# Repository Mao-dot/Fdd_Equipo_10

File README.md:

<h1 align="center">Equipo 10 — Fundamentos de Diseño</h1>

<p align="center">
  <strong>Ingeniería Informática e Ingeniería Industrial · 2026-2</strong><br />
  Universidad Peruana Cayetano Heredia
</p>

---

## Rediseño de FoodScan

- [Modelo 3D y archivos de fabricación](Proyecto/MóduloMecánico/Rediseño/README.md) · [STEP para Onshape](Proyecto/MóduloMecánico/Rediseño/exports/step/FoodScan_cerrado_Onshape.step)
- [Electrónica revisión A](Proyecto/MóduloElectrónico/Rediseño_FoodScan/README.md) · [Esquemático editable en EasyEDA](Proyecto/MóduloElectrónico/Rediseño_FoodScan/easyeda/FoodScan.epro2)
- [Lista de materiales](Proyecto/MóduloElectrónico/BOM.md) · [Integración de la PCB con la carcasa](Proyecto/MóduloElectrónico/Rediseño_FoodScan/Integracion_mecanica.md)
- [Entrega del Taller 11](Fundamentos%20de%20diseño/Talleres/Taller_11.md)

## 🌍 Descripción del Equipo

Somos el **Equipo 10** del curso **Fundamentos de Diseño 2026-2**, conformado por estudiantes de las carreras de Ingeniería Informática e Industrial.
Nuestro objetivo es aplicar la metodología de diseño para generar soluciones innovadoras con impacto social, tecnológico y ambiental.

---

## 🎯 ODS principal: ODS 12 — Producción y consumo responsables

El Objetivo de Desarrollo Sostenible 12 busca garantizar modalidades de consumo y producción sostenibles. Este objetivo promueve el uso responsable de los recursos, la reducción de residuos y el acceso a información que permita a las personas adoptar decisiones de consumo más conscientes.

### Meta seleccionada: 12.8

La meta 12.8 busca garantizar que, para el año 2030, las personas dispongan de información y conocimientos relevantes que les permitan adoptar estilos de vida sostenibles y en armonía con la naturaleza.

---

## ⚠️ Problemática identificada

En la vida cotidiana, las personas que desean controlar y conocer mejor su alimentación presentan dificultades para obtener información práctica, inmediata y comprensible sobre la cantidad y la composición nutricional de los alimentos que consumen.

Aunque existen tablas nutricionales, aplicaciones y bases de datos, estas herramientas suelen presentar valores correspondientes a cantidades estandarizadas, como 100 gramos o porciones predeterminadas. Por ello, el usuario debe identificar el alimento, estimar la cantidad servida, consultar distintas referencias e introducir manualmente los datos. Este proceso requiere tiempo y conocimientos previos, puede producir estimaciones poco consistentes y dificulta mantener un seguimiento frecuente.

Esta situación resulta especialmente relevante para las personas que realizan actividad física y buscan conocer regularmente la composición de sus comidas, principalmente la cantidad de proteínas, carbohidratos y grasas presentes en las porciones que consumen.

Por lo tanto, el problema no es necesariamente la ausencia de información nutricional, sino la dificultad para relacionar la información general disponible con la cantidad real de alimento presente en una porción cotidiana. Esta limitación puede reducir la capacidad de las personas para comparar sus porciones y tomar decisiones informadas y conscientes sobre su consumo.

---

## 👥 Público objetivo

### Público general

Personas interesadas en conocer mejor las cantidades y la composición nutricional de los alimentos que consumen.

### Público inicial

Personas físicamente activas que realizan un seguimiento frecuente de su alimentación y necesitan consultar información sobre las porciones y los macronutrientes presentes en sus comidas.

---

## 🔗 Relación de la problemática con el ODS 12

La problemática se relaciona con el ODS 12 porque el acceso a información comprensible sobre los alimentos y sus porciones puede favorecer decisiones de consumo más informadas y conscientes.

En particular, se vincula con la meta 12.8, ya que esta plantea la necesidad de que las personas dispongan de información y conocimientos relevantes para adoptar hábitos de consumo responsables. El equipo se enfocará inicialmente en comprender las dificultades que encuentran los usuarios al intentar obtener y utilizar esta información, antes de definir una solución o prototipo.

Para precisar su vínculo con el consumo sostenible, el equipo analizará también si las dificultades para comprender y estimar las porciones influyen en la planificación de las cantidades consumidas y en decisiones que puedan producir consumo excesivo o desperdicio de alimentos. Esta relación se estudiará como parte de la problemática y no se asumirá como un resultado previo.

---

## ❓ Pregunta de investigación

> ¿Cómo facilitar que las personas que desean iniciar o mantener una alimentación controlada reconozcan de manera práctica las cantidades y composición nutricional de los alimentos que consumen? 

---

## 📍 Alcance inicial

El proyecto estudiará el acceso y uso de información nutricional relacionada con porciones cotidianas. En esta etapa no se planteará una solución definitiva ni se abordarán diagnósticos médicos, tratamientos o planes de alimentación personalizados.

---

## 📚 Referencias

1. Naciones Unidas. [Objetivo de Desarrollo Sostenible 12: Producción y consumo responsables](https://sdgs.un.org/goals/goal12).
2. Instituto Nacional de Salud. [Porciones recomendadas](https://alimentacionsaludable.ins.gob.pe/adultos/porciones-recomendadas).
3. Instituto Nacional de Salud. [Aplicación Tablas Peruanas de Composición de Alimentos](https://www.gob.pe/es/38805-acceder-a-informacion-alimenticia-en-la-aplicacion-tablas-peruanas-de-composicion-de-alimentos).
4. Organización de las Naciones Unidas para la Alimentación y la Agricultura. [Food Composition Data: Production, Management and Use](https://www.fao.org/uploads/media/Greenfield_and_shouthgate_2003_English_02.pdf).

---

## 📸 Fotografía del Equipo

---

## 👥 Integrantes del Equipo
| Foto | Nombre | Rol | Intereses |
|:---:|--------|-----|-----------|
|  | **Mao Arceni Capcha Pumacahua** | Líder del equipo | Programación, análisis de datos, simulación |
|  | **Cruz Oyarce Katherine Jireh** | Encargado de documentación | comunicación científica y redacción técnica |
|  | **Lucero Sofía Tarazona Gonzales** | Responsable de investigación | Gestión ambiental, desarrollo comunitario |
|  | **Renzo Jair Cruz Vega** | Diseñador | Diseño de prototipos, creatividad aplicada |
|  | **Julio Maguiña** | Coordinador de investigación | Investigación, análisis y desarrollo de propuestas |

---

## 📌 Resumen Final
Este README resume quiénes somos, el ODS principal seleccionado y la problemática que buscamos comprender durante el curso.

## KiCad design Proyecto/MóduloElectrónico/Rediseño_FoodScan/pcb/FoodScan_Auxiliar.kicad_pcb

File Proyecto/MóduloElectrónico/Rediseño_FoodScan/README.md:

# FoodScan · Rediseño electrónico

Revisión A para prototipo, 12 de noviembre de 2026. La entrega parte de la BOM del rediseño y de su ensamblaje mecánico de trabajo. El sistema utiliza la Adafruit 5838, una DevKitC-1 N16R8 v1.1, el módulo UART Best Modules BMH12M205, el OLED Waveshare 25742 y cuatro tiras COB.

| Archivo | Uso |
| --- | --- |
| [FoodScan.epro2](easyeda/FoodScan.epro2) | Proyecto nativo para EasyEDA Pro 3.2.209, con cuatro hojas, símbolos, huellas y PCB de dos capas enrutada. |
| [Vistas de esquemático](easyeda/vistas/) | Hojas de PCB auxiliar, entrada e iluminación, ESP32 y cámara, y pesaje, pantalla y controles. |
| [PCB editable de KiCad](pcb/FoodScan_Auxiliar.kicad_pcb) | Fuente física de la placa. Las bibliotecas `.pretty`, el archivo `fp-lib-table` y los STEP individuales se incluyen al lado. |
| [STEP poblado](pcb/FoodScan_Auxiliar.step) · [Vista 3D](pcb/FoodScan_Auxiliar.png) | Exportación de la PCB real, para revisar el montaje e incorporarla al ensamblaje. |
| [BOM](BOM.md) · [Fuentes comerciales](fuentes/README.md) | Referencias de compra, documentación, biblioteca y modelos de origen. |
| [Matriz de pines y redes](Matriz_conexiones.csv) · [Matriz de arneses](Matriz_arneses.csv) | Numeración de pines y 66 conexiones físicas de extremo a extremo, incluidos retornos y empalmes. |
| [Verificación eléctrica](Verificacion_electrica.md) · [Integración mecánica](Integracion_mecanica.md) | Cálculos y comprobaciones realizadas, límites y procedimiento para el banco. |
| [Informe DRC](validacion/DRC_KiCad.json) · [Verificación del proyecto](easyeda/Verificacion_EasyEDA.json) | Resultados de KiCad y del conversor local de EasyEDA. |

## Abrir en EasyEDA Pro

1. Descarga `easyeda/FoodScan.epro2`. En EasyEDA Pro 3.2.209, usa **File → Import → EasyEDA (Professional)** e importa el archivo como proyecto nuevo. El proyecto incluye los símbolos y huellas necesarios. Para reutilizarlos en otro proyecto, usa la extracción de biblioteca de la importación si tu modo de trabajo la ofrece. [Guía de importación](https://prodocs.easyeda.com/en/import-export/export-easyeda-pro/) · [Notas de la versión](https://prodocs.easyeda.com/en/faq/update-record/)
2. Abre las cuatro hojas y la PCB desde el árbol. Comprueba que haya 29 referencias eléctricas en la placa, cuatro agujeros, dos polígonos de GND y el contorno de 60 × 65 mm. Desde el esquemático usa **Design → Check DRC** y revisa la lista de cambios de **Update/Convert Schematic to PCB**. Los módulos comerciales y los elementos de panel deben figurar como externos. Comprueba los cambios en una copia antes de aplicarlos. [Reglas de esquemático](https://prodocs.easyeda.com/en/schematic/design-design-rule/) · [Actualización de PCB](https://prodocs.easyeda.com/en/schematic/design-update-convert-schematic-to-pcb/)
3. En el PCB, ajusta las reglas a las especificaciones del fabricante, reconstruye los dos polígonos de GND y ejecuta **Design → Check DRC**. Revisa el resultado y compáralo con el archivo de KiCad y la matriz. [Guía de DRC](https://prodocs.easyeda.com/en/pcb/design-check-drc/)
4. El STEP poblado está disponible directamente para CAD. Para regenerar el STEP desde EasyEDA, importa los STEP individuales, asígnalos en **Tools → 3D Model Manager** y verifica pin 1, cara superior y asiento sobre la PCB. Las transformaciones verificadas para la exportación se encuentran en los modelos de la placa KiCad. Los modelos KiCad usan la transformación de su huella y escala unitaria. Para RECOM, usa el STEP OEM, giro de 180° sobre X y ajuste de origen respecto al pad 1 según [integración mecánica](Integracion_mecanica.md). Exporta **Export → 3D File → STEP**, con PCB y componentes activados. La asociación de STEP dentro de EasyEDA queda pendiente de esta comprobación en el editor. [Gestor 3D](https://prodocs.easyeda.com/en/pcb/tools-3d-model-manager/) · [Exportación STEP](https://prodocs.easyeda.com/en/pcb/export-3d-file/)

## Decisiones de circuito y montaje

- **Pesaje.** J4 lleva GND, 3,3 V, TXD y RXD al BMH12M205. J9 lleva UART y masa a la DevKitC. Los cuatro hilos de puente forman parte del conjunto comercial y el arnés externo tiene cuatro vías digitales. La interconexión se cablea según la numeración OEM, cruzando TX y RX. [Manual Best Modules](https://www.bestmodulescorp.com/en/amfile/file/download/file/2030/product/1300/)
- **Cámara y pantalla.** El DVP y SCCB van directamente a la DevKitC por un arnés corto. La alimentación sale de la placa auxiliar. El puente XCLK del 5838 se configura a INT de 24 MHz y VM se cierra para el actuador de autofocus. El OLED conserva el SPI de fábrica y usa 3,3 V de U2. Confirmar la versión de firmware y los niveles de señal con los arneses definitivos. [Adafruit](https://learn.adafruit.com/adafruit-ov5640-camera-breakout/pinouts) · [Waveshare](https://www.waveshare.com/wiki/2.42inch_OLED_Module)
- **Alimentación y puerta.** Un RECOM dedicado alimenta los periféricos. Dos AO3400A separan los retornos de las tiras en pares. El detector NC y su resistencia al final del arnés permiten distinguir el cierre de la desconexión. La posición de P39 requiere ajuste y la tensión sobre el contacto debe calificarse. El fusible T4 A y el comportamiento de limitación del adaptador siguen sujetos a ensayo. [Verificación de diseño y pasos de banco](Verificacion_electrica.md)
- **Bibliotecas y geometría.** Se reutilizaron símbolos de EasyEDA/LCSC, el símbolo comunitario cotejado del DevKit y fuentes OEM de Adafruit. Los símbolos de interfaz documentados de los módulos externos se basan en sus pines oficiales. Las huellas incompatibles de catálogo se sustituyeron por huellas KiCad con paso correcto y la huella RECOM se construyó con el plano OEM. El STEP poblado usa el STEP OEM de RECOM y los modelos de biblioteca de los conectores y encapsulados montados. Los modelos disponibles de OLED, detector y jack son de fabricante. El STEP completo de la cámara, la DevKitC y el pesaje sigue sin una fuente exacta verificable. [Inventario de fuentes](fuentes/README.md)

## Estado de verificación

El conversor incluido en EasyEDA reabrió el proyecto y conservó las cuatro hojas, 45 símbolos colocados y la geometría de la PCB. Su exportación de lista de redes coincidió con las 35 redes y los 162 terminales conectados de la matriz. La verificación local cotejó los pads y los 17 terminales intencionalmente libres. El DRC de KiCad 10.0.8 sobre la placa fuente reportó **0 infracciones y 0 conexiones pendientes**. La PCB tiene 241 segmentos de pista, 10 vías y dos planos de GND. La visualización y el STEP proceden de esa placa.

La entrega sirve para revisión de prototipo. Quedan pendientes la importación y ERC/DRC en el editor de EasyEDA, el enlace 3D en EasyEDA y las pruebas de banco y de montaje. Para alimentar por USB durante programación, desconecta la DevKitC de la alimentación y señales del sistema.

## Reproducir

Para recuperar las bibliotecas de origen y el STEP del regulador RECOM, ejecutar `python fuentes/descargar_bibliotecas.py`. [Fuentes y descargas](fuentes/README.md)

`herramientas/definir_circuito.py` genera la matriz y `herramientas/definir_arneses.py` valida los arneses con ella. `herramientas/generar_pcb.py` usa Python, NumPy, sexpdata y la carpeta `share/kicad` de KiCad 10. Tras generarla, rellena zonas y guarda con `kicad-cli pcb drc --refill-zones --save-board`. Luego ejecuta `python herramientas/generar_easyeda.py --pcb pcb/FoodScan_Auxiliar.kicad_pcb` desde esta carpeta. El generador usa Node.js y el conversor de la instalación local de EasyEDA 3.2.209. Exporta el STEP con origen de usuario `80x135mm`.

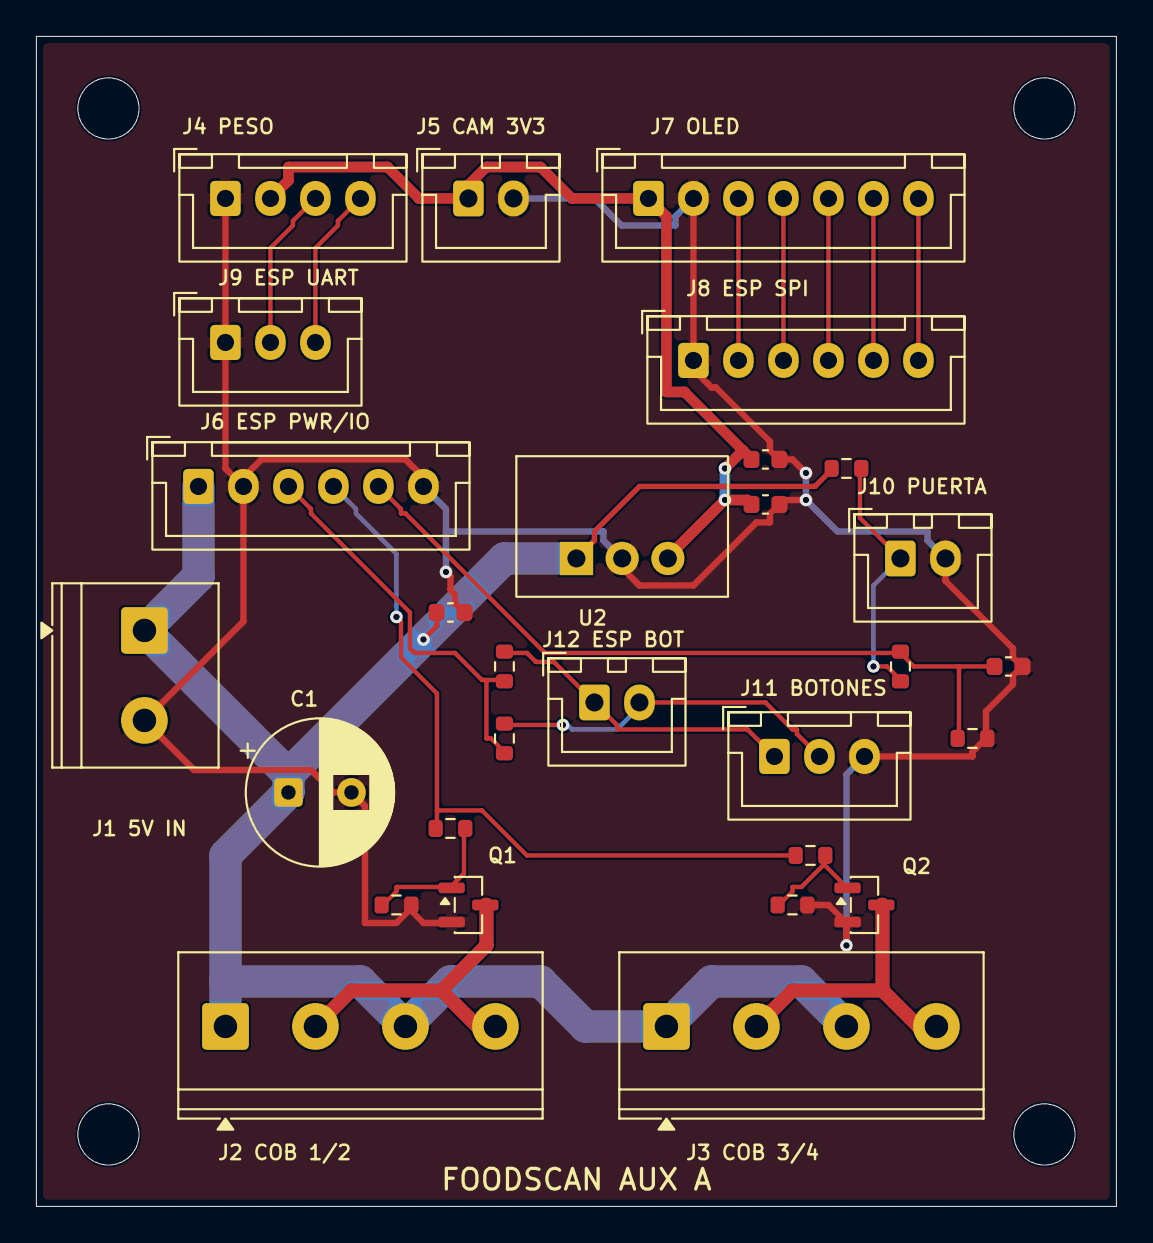
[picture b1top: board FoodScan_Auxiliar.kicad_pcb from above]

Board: 2 copper layers, 60.0 x 65.0 mm, 33 parts (0 on the bottom side), 20 nets.

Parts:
C1: 470 uF / 16 V; CP_Radial_D8.0mm_P3.50mm
C2, C3: 10 uF / 10 V; C_0603_1608Metric
C4, C5: 100 nF / 50 V; C_0603_1608Metric
H1, H2, H3, H4: NPTH 3.4 mm; NPTH_3.4mm_M3
J1: 1935161; TerminalBlock_Phoenix_PT-1,5-2-5.0-H_1x02_P5.00mm_Horizontal
J2, J3: 1935187; TerminalBlock_Phoenix_PT-1,5-4-5.0-H_1x04_P5.00mm_Horizontal
J4: B4B-XH-A(LF)(SN); JST_XH_B4B-XH-A_1x04_P2.50mm_Vertical
J5, J10, J12: B2B-XH-A(LF)(SN); JST_XH_B2B-XH-A_1x02_P2.50mm_Vertical
J6, J8: B6B-XH-A(LF)(SN); JST_XH_B6B-XH-A_1x06_P2.50mm_Vertical
J7: B7B-XH-A(LF)(SN); JST_XH_B7B-XH-A_1x07_P2.50mm_Vertical
J9, J11: B3B-XH-A(LF)(SN); JST_XH_B3B-XH-A_1x03_P2.50mm_Vertical
Q1, Q2: AO3400A; SOT-23
R1, R2: 100 ohm; R_0603_1608Metric
R3, R4: 100 kohm; R_0603_1608Metric
R5: 2.2 kohm; R_0603_1608Metric
R6, R7, R8, R10: 10 kohm; R_0603_1608Metric
U2: R-78K3.3-1.0; RECOM_R-78K-1.0

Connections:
3V3_AUX: C3.1, C4.1, J4.2, J5.1, J7.1, U2.3
3V3_ESP: J6.3, R8.1, R10.1
5V_SW: C1.1, C2.1, J1.1, J2.1, J2.3, J3.1, J3.3, J6.1, R5.1, U2.1
CAPTURA_N: J11.2, J12.2, R10.2
GND: C1.2, C2.2, C3.2, C4.2, C5.2, J1.2, J4.1, J5.2, J6.2, J6.6, J7.2, J8.1, J9.1, J10.2, J11.3, Q1.2, Q2.2, R3.2, R4.2, R7.2, U2.2
LED_EN: J6.4, R1.1, R2.1
LED_GATE_A: Q1.1, R1.2, R3.1
LED_GATE_B: Q2.1, R2.2, R4.1
LED_RET_A: J2.2, J2.4, Q1.3
LED_RET_B: J3.2, J3.4, Q2.3
OLED_CLK: J7.4, J8.3
OLED_CS_N: J7.5, J8.4
OLED_DC: J7.6, J8.5
OLED_DIN: J7.3, J8.2
OLED_RST_N: J7.7, J8.6
PESO_RX: J4.4, J9.3
PESO_TX: J4.3, J9.2
PUERTA_5V: J10.1, R5.2, R6.1
PUERTA_ADC: C5.1, J6.5, R6.2, R7.1
TARA_N: J11.1, J12.1, R8.2
